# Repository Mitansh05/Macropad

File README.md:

# My Macropad

This is my open source 9-key macropad, this project is mainly built around the **Seeed Studio XIAO RP2040**, but I have also provided some files that will help you if you want to use the **Micro Pico**.

## Author

- [@Mitansh05](https://github.com/Mitansh05)

## PCB

### Try it yourself

### Schematic / PCB imgs

#### Alt approch to the PCB:

## Getting Started - Firmware / setup

- Step 1: Install **CircuitPython**.
- Step 2: Hold down the physical **`BOOT`** / **`BOOTSEL`** button on your Seeed XIAO board.
- Step 3: Drag and drop all of the files inside `Firmware` folder (`kmk`, `boot.py`, `code.py`, `keymap.py`) into the **CIRCUITPY** inside the XIAO.
- Step 4: Safely eject the drive from your decvice, physically unplug the USB cable from the XIAO for ~3sec and then plug it back in to make sure the macros are initialized.

### Active Layout Blueprint

This is the 9 key layout that is pre-loaded on the macropad.

| Left Column                     | Center Column                    | Right Column                   |
| :------------------------------ | :------------------------------- | :----------------------------- |
| **📑 Copy**<br>`Pin D0`         | **📋 Paste**<br>`Pin D1`         | **📊 Calculator**<br>`Pin D2`  |
| **🎵 Play / Pause**<br>`Pin D3` | **⏮️ Prev Track**<br>`Pin D4`    | **🔇 Panic Mute**<br>`Pin D5`  |
| **🛠️ Task Manager**<br>`Pin D6` | **✂️ Snipping Tool**<br>`Pin D7` | **🔒 Lock Screen**<br>`Pin D8` |

## Resources Used

[HackClub HackPad](https://hackpad.hackclub.com/guide)

[KiCad](https://www.kicad.org/)

### Additional info

- Docunmentation can be found on [HackClub](https://stardance.hackclub.com/projects/44402)

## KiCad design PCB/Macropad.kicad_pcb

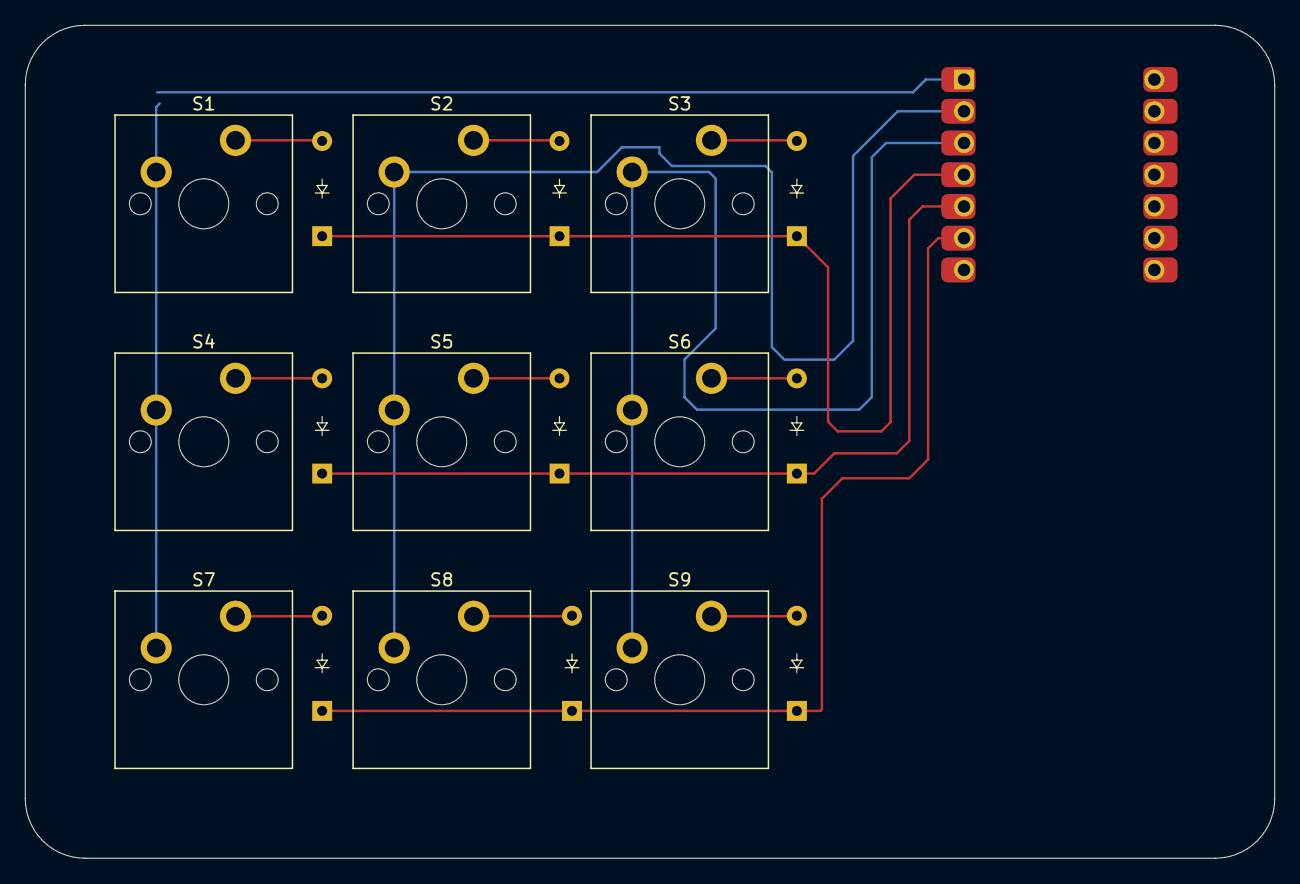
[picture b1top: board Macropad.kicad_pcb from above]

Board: 2 copper layers, 100.0 x 66.7 mm, 19 parts (0 on the bottom side), 15 nets.

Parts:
D1, D2, D3, D4, D5, D6, D7, D8, D9: Diode_DO-35
S1, S2, S3, S4, S5, S6, S7, S8, S9: MX_PCB_1.00u
U2: MOUDLE-SEEEDUINO-XIAO; Seeed_XIAO_RP2040

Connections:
Column 0: S1.1, S4.1, S7.1, U2.1 (PA02_A0_D0)
Column 1: S2.1, S5.1, S8.1, U2.2 (PA4_A1_D1)
Column 2: S3.1, S6.1, S9.1, U2.3 (PA10_A2_D2)
unnamed: D1.2 (A), S1.2
unnamed: D2.2 (A), S2.2
unnamed: D3.2 (A), S3.2
unnamed: D4.2 (A), S4.2
unnamed: D5.2 (A), S5.2
unnamed: D6.2 (A), S6.2
unnamed: D7.2 (A), S7.2
unnamed: D8.2 (A), S8.2
unnamed: D9.2 (A), S9.2
Row 0: D1.1 (K), D2.1 (K), D3.1 (K), U2.4 (PA11_A3_D3)
Row 1: D4.1 (K), D5.1 (K), D6.1 (K), U2.5 (PA8_A4_D4_SDA)
Row 2: D7.1 (K), D8.1 (K), D9.1 (K), U2.6 (PA9_A5_D5_SCL)

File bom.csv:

Designator,Footprint,Quantity,Value,LCSC Part #
"D1, D2, D3, D4, D5, D6, D7, D8, D9",Diode_DO-35,9,~,
"S1, S2, S3, S4, S5, S6, S7, S8, S9",MX_PCB_1.00u,9,~,
U2,Seeed_XIAO_RP2040,1,MOUDLE-SEEEDUINO-XIAO,
